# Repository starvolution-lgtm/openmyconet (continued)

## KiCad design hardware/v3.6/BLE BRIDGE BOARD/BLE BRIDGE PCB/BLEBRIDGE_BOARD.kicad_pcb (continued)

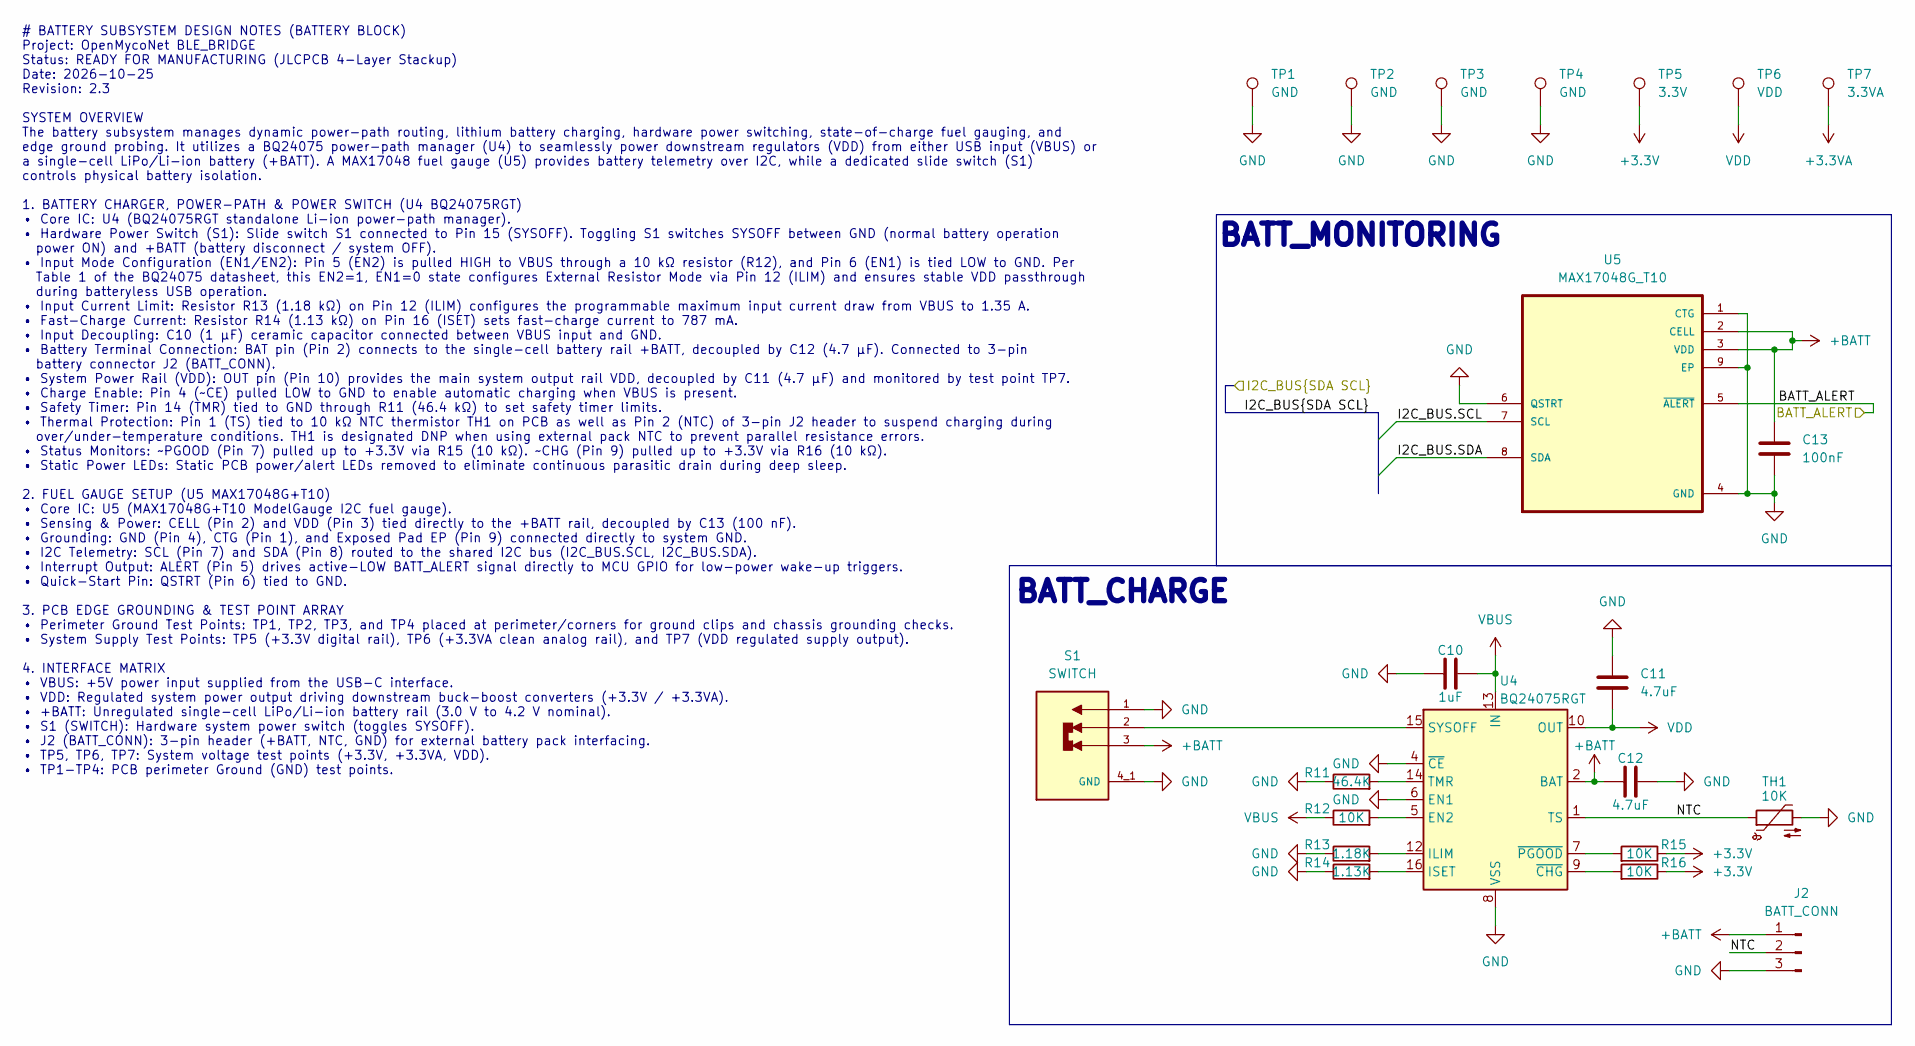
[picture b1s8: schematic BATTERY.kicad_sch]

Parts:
C10: 1uF; C_0805_2012Metric
C11, C12: 4.7uF; C_0805_2012Metric
C13: 100nF; C_0603_1608Metric
J2: BATT_CONN; JST_XH_B3B-XH-A_1x03_P2.50mm_Vertical
R11: 46.4K; R_0603_1608Metric
R12, R15, R16: 10K; R_0603_1608Metric
R13: 1.18K; R_0603_1608Metric
R14: 1.13K; R_0603_1608Metric
S1: SWITCH; SW_MSK12C02; PARTREV A/0
TH1: 10K; R_0805_2012Metric
TP1, TP2, TP3, TP4: GND; TestPoint_Plated_Hole_D2.0mm
TP5: 3.3V; TestPoint_Pad_1.0x1.0mm
TP6: VDD; TestPoint_Pad_1.0x1.0mm
TP7: 3.3VA; TestPoint_Pad_1.0x1.0mm
U4: BQ24075RGT; VQFN-16-1EP_3x3mm_P0.5mm_EP1.6x1.6mm
U5: MAX17048G_T10; SON50P200X200X80-9N

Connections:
+3.3V: R15.1, R16.1, TP5.1 (1_1); also elsewhere on the board
+3.3VA: TP7.1 (1_1); also elsewhere on the board
+BATT: C12.2, C13.1, J2.1, S1.3, U4.2 (BAT), U4.3 (BAT), U5.2 (CELL), U5.3 (VDD)
/BLOCK_DIAGRAM//BATT_ALERT: U5.5 (~ALERT); also elsewhere on the board
/BLOCK_DIAGRAM//I2C_BUS.SCL: U5.7 (SCL); also elsewhere on the board
/BLOCK_DIAGRAM//I2C_BUS.SDA: U5.8 (SDA); also elsewhere on the board
/BLOCK_DIAGRAM/BATTERY/NTC: J2.2, TH1.1, U4.1 (TS)
GND: C10.2, C11.1, C12.1, C13.2, J2.3, R11.1, R13.1, R14.1, S1.1, S1.4_1 (GND), S1.4_2 (GND), S1.4_3 (GND), S1.4_4 (GND), TH1.2, TP1.1 (1_1), TP2.1 (1_1), TP3.1 (1_1), TP4.1 (1_1), U4.4 (~CE), U4.6 (EN1), U4.8 (VSS), U4.17 (VSS), U5.1 (CTG), U5.4 (GND), U5.6 (QSTRT), U5.9 (EP); also elsewhere on the board
unnamed: R12.2, U4.5 (EN2)
unnamed: R13.2, U4.12 (ILIM)
unnamed: R14.2, U4.16 (ISET)
unnamed: S1.2, U4.15 (SYSOFF)
unnamed: R11.2, U4.14 (TMR)
unnamed: R16.2, U4.9 (~CHG)
unnamed: R15.2, U4.7 (~PGOOD)
VBUS: C10.1, R12.1, U4.13 (IN); also elsewhere on the board
VDD: C11.2, TP6.1 (1_1), U4.10 (OUT), U4.11 (OUT); also elsewhere on the board

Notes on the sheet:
BATT_CHARGE
# BATTERY SUBSYSTEM DESIGN NOTES (BATTERY BLOCK) Project: OpenMycoNet BLE_BRIDGE Status: READY FOR MANUFACTURING (JLCPCB 4-Layer Stackup) Date: 2026-10-25 Revision: 2.3 SYSTEM OVERVIEW The battery subsystem manages dynamic power-path routing, lithium battery charging, hardware power switching, stat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
BATT_MONITORING

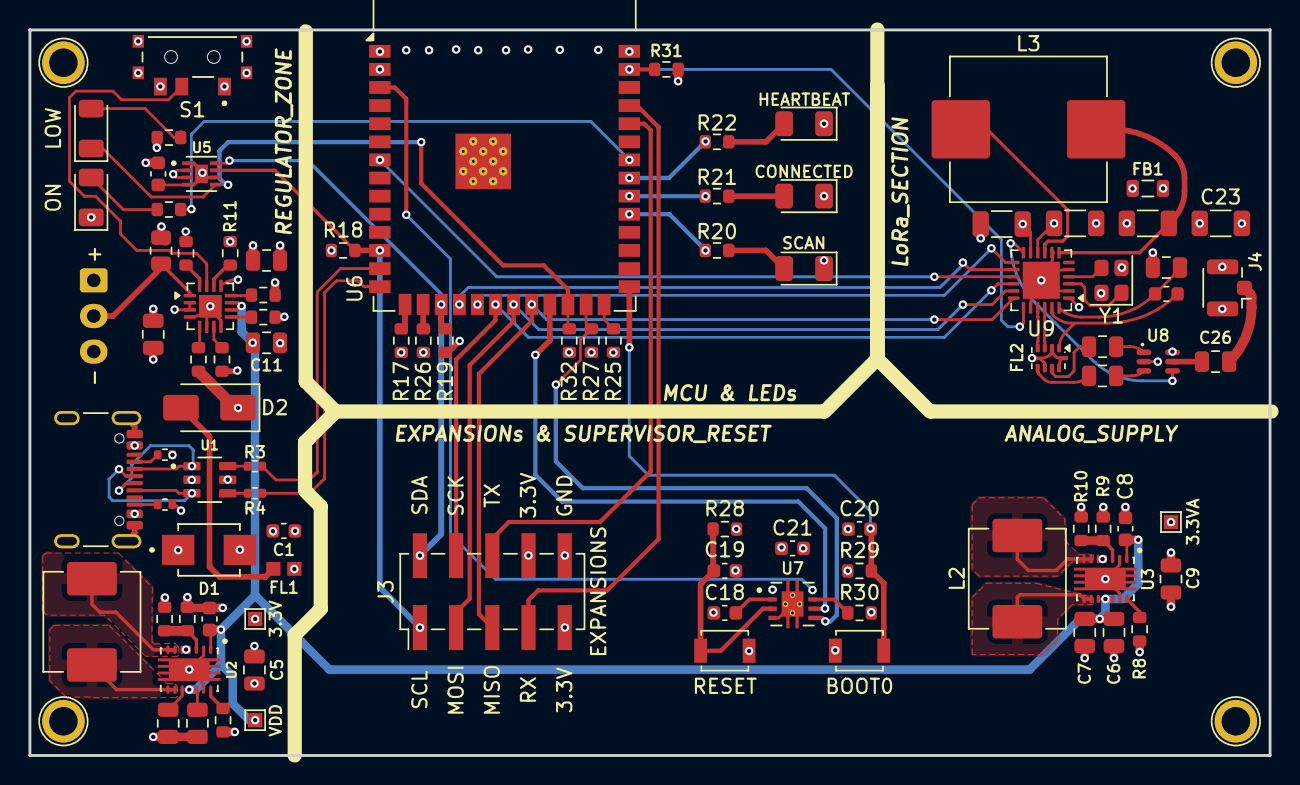
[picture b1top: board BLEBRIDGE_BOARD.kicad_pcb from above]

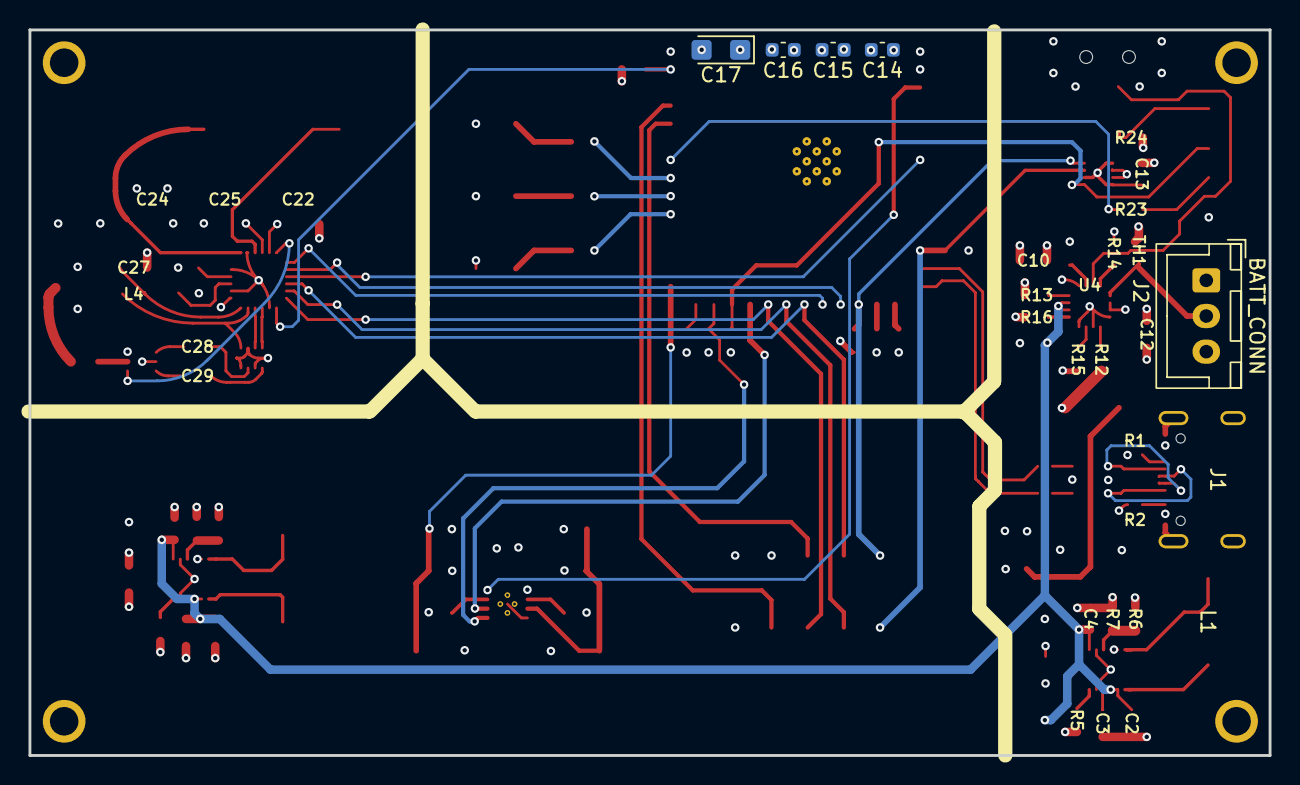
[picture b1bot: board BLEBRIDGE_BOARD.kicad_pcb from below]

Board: 4 copper layers, 87.0 x 50.9 mm, 100 parts (5 on the bottom side), 79 nets.

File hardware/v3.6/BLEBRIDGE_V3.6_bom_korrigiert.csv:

Designator,Footprint,Quantity,Value,LCSC Part #
"C1, C13, C14, C15, C16, C18, C19, C20, C21, C4, C8",603,11,100nF,
C10,805,1,1uF,
"C11, C12",805,2,4.7uF,
C17,CP_EIA-3216-18_Kemet-A,1,10uF,C7171
"C2, C3, C5, C6, C7, C9",805,6,10uF,
C22,1206,1,10uF,
C23,1206,1,100nF,
C24,1206,1,470nF,
C25,1206,1,47uF,
"C26, C28, C29",805,3,47pF,
C27,805,1,100nF,
D1,SMBJ5.0A,1,SMBJ5.0A,C83333
D2,D_SMA,1,SS34,C8678
D3,1206,1,LOW,C28310439
D4,1206,1,SCAN,C28310438
D5,1206,1,CONNECTED,C30584802
D6,1206,1,HEARTBEAT,C28310440
D7,1206,1,ON,C30584801
FB1,805,1,FerriteBead_Small,
FL1,BEADC1608X95N,1,BLM18PG121SN1D,C14709
FL2,Balun_Johanson_0900FM15K0039,1,0900FM15K0039,C7434807
J1,USB_C_Receptacle_GCT_USB4105-xx-A_16P_TopMnt_Horizontal,1,USB_C_Receptacle_USB2.0_16P,C2765186
J2,JST_XH_B3B-XH-A_1x03_P2.50mm_Vertical,1,BATT_CONN,C144394
J3,PinHeader_2x05_P2.54mm_Vertical_SMD,1,EXPANSIONS,C55213916
J4,U.FL_Hirose_U.FL-R-SMT-1_Vertical,1,Conn_Coaxial_Small,C88374
"L1, L2",L_APV_APH0630,2,1.5uH,C5349697
L3,L_APV_APH1040,1,15uH,C5349716
L4,603,1,27nH,C6807996
"R1, R2",402,2,5.1K,
"R10, R7",603,2,180K,
R11,603,1,46.4K,
"R12, R15, R16, R17, R25, R26, R28, R29, R31, R32",603,10,10K,
R13,603,1,1.18K,
R14,603,1,1.13K,
"R18, R19",603,2,4.7K,
"R20, R21, R22, R23, R24",603,5,1K,
"R27, R30, R5, R8",603,4,100K,
"R3, R4",402,2,27,
"R6, R9",603,2,1M,
S1,SW_MSK12C02,1,SWITCH,C431540
SW1,SW_SPST_B3U-1000P,1,RESET,C231329
SW2,SW_SPST_B3U-1000P,1,BOOT0,C231329
"TP1, TP2, TP3, TP4",TestPoint_Plated_Hole_D2.0mm,4,GND,
TP5,TestPoint_Pad_1.0x1.0mm,1,3.3V,
TP6,TestPoint_Pad_1.0x1.0mm,1,VDD,
TP7,TestPoint_Pad_1.0x1.0mm,1,3.3VA,
U1,USBLC6-2SC6,1,USBLC6-2SC6,C7519
"U2, U3",IC_TPS63020DSJT,2,TPS63020DSJR,C15483
U4,VQFN-16-1EP_3x3mm_P0.5mm_EP1.6x1.6mm,1,BQ24075RGT,C2865459
U5,SON50P200X200X80-9N,1,MAX17048G_T10,C2682616
U6,ESP32-S3-WROOM-1,1,ESP32-S3-WROOM-1-N16R8,C2913202
U7,IC_DRV8601DRBT,1,TPS3851H33EDRBR,C717624
U8,SOT65P215X110-6N,1,PE4259,C470892
U9,QFN-24-1EP_4x4mm_P0.5mm_EP2.6x2.6mm,1,SX1262IMLTRT,C191341
Y1,Crystal_SMD_2520-4Pin_2.5x2.0mm,1,32MHz,C2842280

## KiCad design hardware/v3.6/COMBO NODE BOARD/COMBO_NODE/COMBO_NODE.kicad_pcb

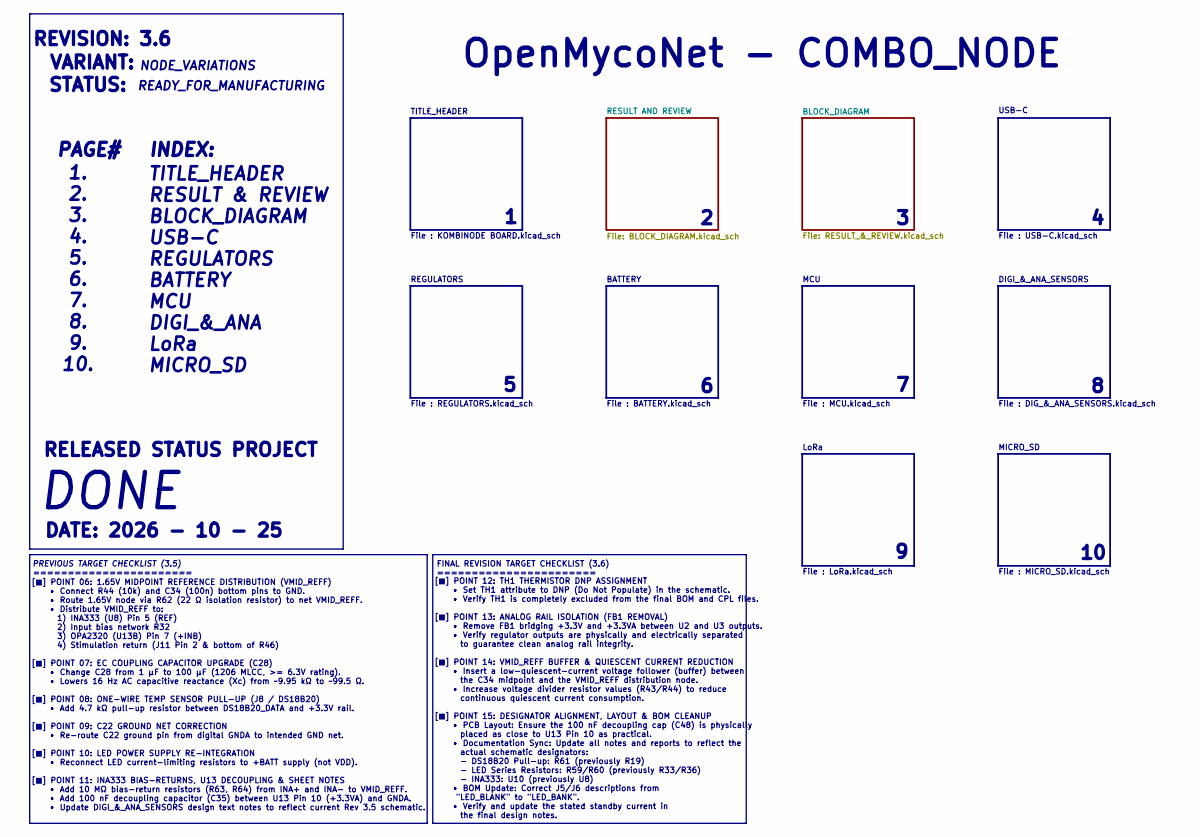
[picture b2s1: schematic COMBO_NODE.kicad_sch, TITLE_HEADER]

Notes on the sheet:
PAGE#
PREVIOUS TARGET CHECKLIST (3.5) =======================
File : LoRa.kicad_sch
MICRO_SD
USB-C
NODE_VARIATIONS
TITLE_HEADER
VARIANT:
File : MICRO_SD.kicad_sch
MCU
File : REGULATORS.kicad_sch
FINAL REVISION TARGET CHECKLIST (3.6) =======================
File : KOMBINODE BOARD.kicad_sch
INDEX:
REVISION: 3.6
BATTERY
STATUS:
DIGI_&_ANA_SENSORS
DONE
READY_FOR_MANUFACTURING
TITLE_HEADER RESULT & REVIEW BLOCK_DIAGRAM USB-C REGULATORS BATTERY MCU DIGI_&_ANA LoRa MICRO_SD
File : BATTERY.kicad_sch
[■] POINT 06: 1.65V MIDPOINT REFERENCE DISTRIBUTION (VMID_REFF) • Connect R44 (10k) and C34 (100n) bottom pins to GND. • Route 1.65V node via R62 (22 Ω isolation resistor) to net VMID_REFF. • Distribute VMID_REFF to: 1) INA333 (U8) Pin 5 (REF) 2) Input bias network R32 3) OPA2320 (U13B) Pin 7 (+INB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
File : MCU.kicad_sch
RELEASED STATUS PROJECT
DATE: 2026 - 10 - 25
LoRa
[■] POINT 12: TH1 THERMISTOR DNP ASSIGNMENT • Set TH1 attribute to DNP (Do Not Populate) in the schematic. • Verify TH1 is completely excluded from the final BOM and CPL files. [■] POINT 13: ANALOG RAIL ISOLATION (FB1 REMOVAL) • Remove FB1 bridging +3.3V and +3.3VA between U2 and U3 outputs. • Veri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
1. 2. 3. 4. 5. 6. 7. 8. 9. 10.
OpenMycoNet - COMBO_NODE
REGULATORS
File : USB-C.kicad_sch
File : DIG_&_ANA_SENSORS.kicad_sch

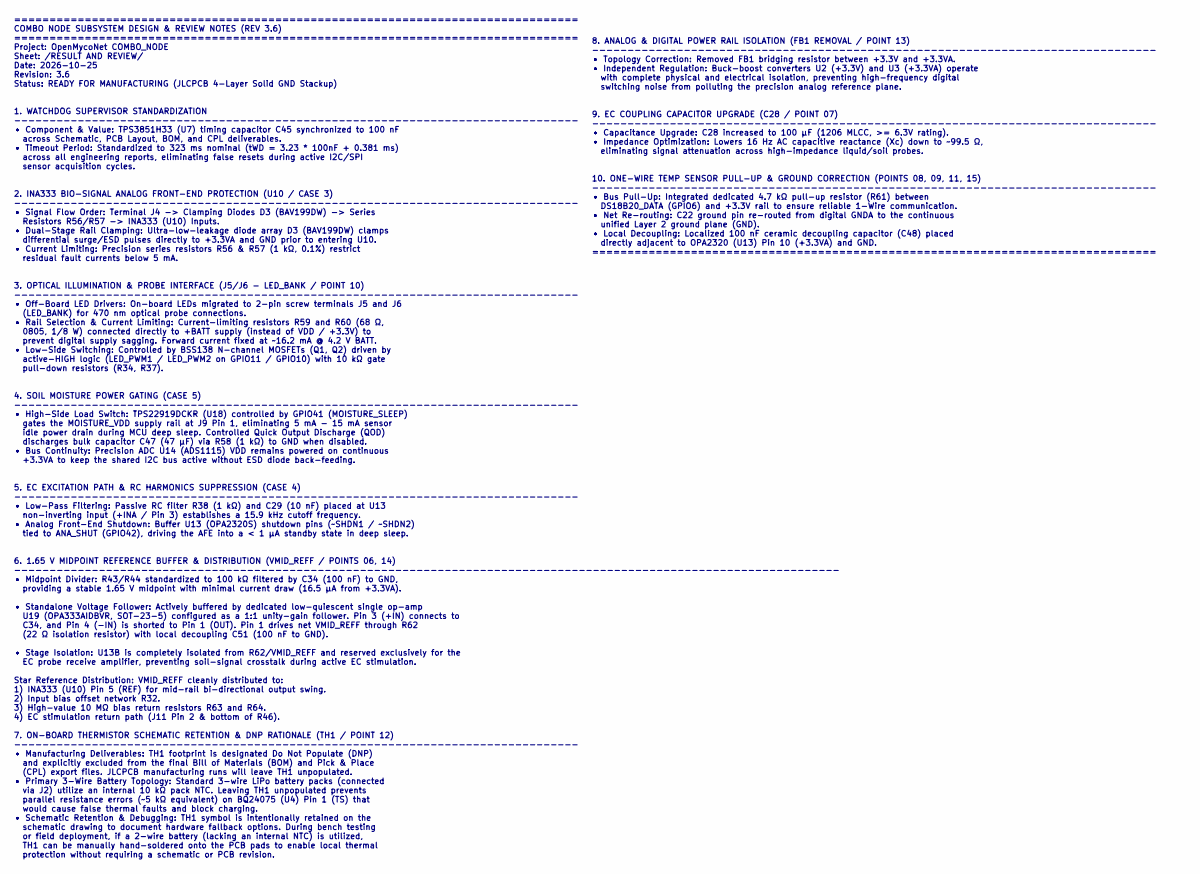
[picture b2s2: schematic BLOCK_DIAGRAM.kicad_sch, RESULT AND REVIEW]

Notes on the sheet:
8. ANALOG & DIGITAL POWER RAIL ISOLATION (FB1 REMOVAL / POINT 13) -------------------------------------------------------------------------------- • Topology Correction: Removed FB1 bridging resistor between +3.3V and +3.3VA. • Independent Regulation: Buck-boost converters U2 (+3.3V) and U3 (+3.3VA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
================================================================================ COMBO NODE SUBSYSTEM DESIGN & REVIEW NOTES (REV 3.6) ================================================================================ Project: OpenMycoNet COMBO_NODE Sheet: /RESULT AND REVIEW/ Date: 2026-10-25 Revision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

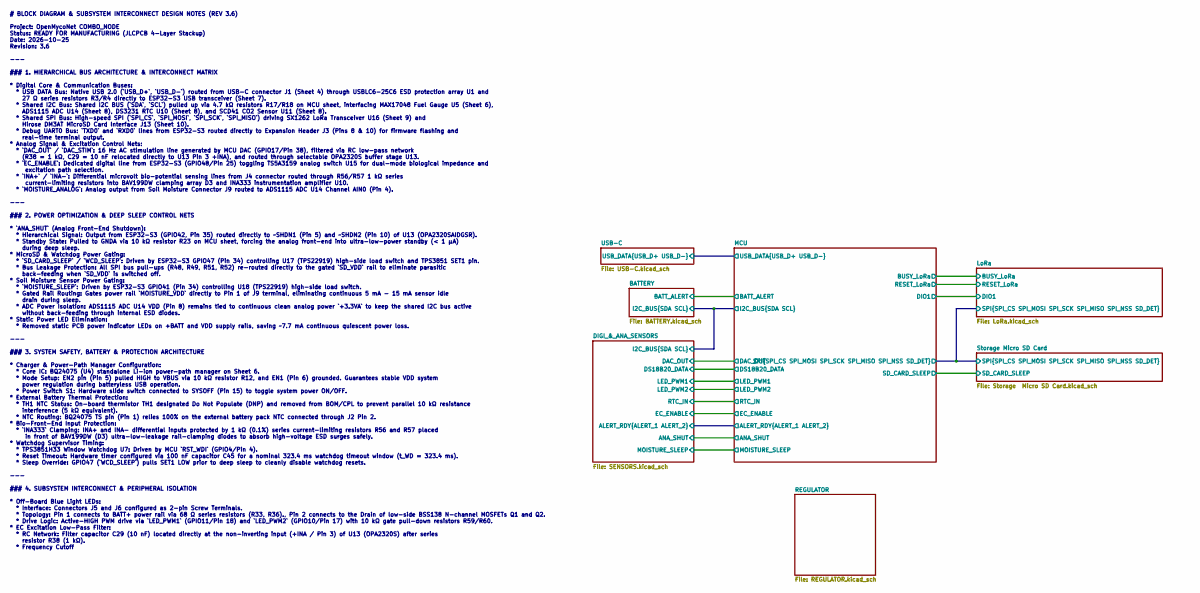
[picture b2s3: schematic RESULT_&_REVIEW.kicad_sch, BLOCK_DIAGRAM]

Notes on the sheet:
# BLOCK DIAGRAM & SUBSYSTEM INTERCONNECT DESIGN NOTES (REV 3.6) Project: OpenMycoNet COMBO_NODE Status: READY FOR MANUFACTURING (JLCPCB 4-Layer Stackup) Date: 2026-10-25 Revision: 3.6 --- ### 1. HIERARCHICAL BUS ARCHITECTURE & INTERCONNECT MATRIX * Digital Core & Communication Buses: * USB DATA Bus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

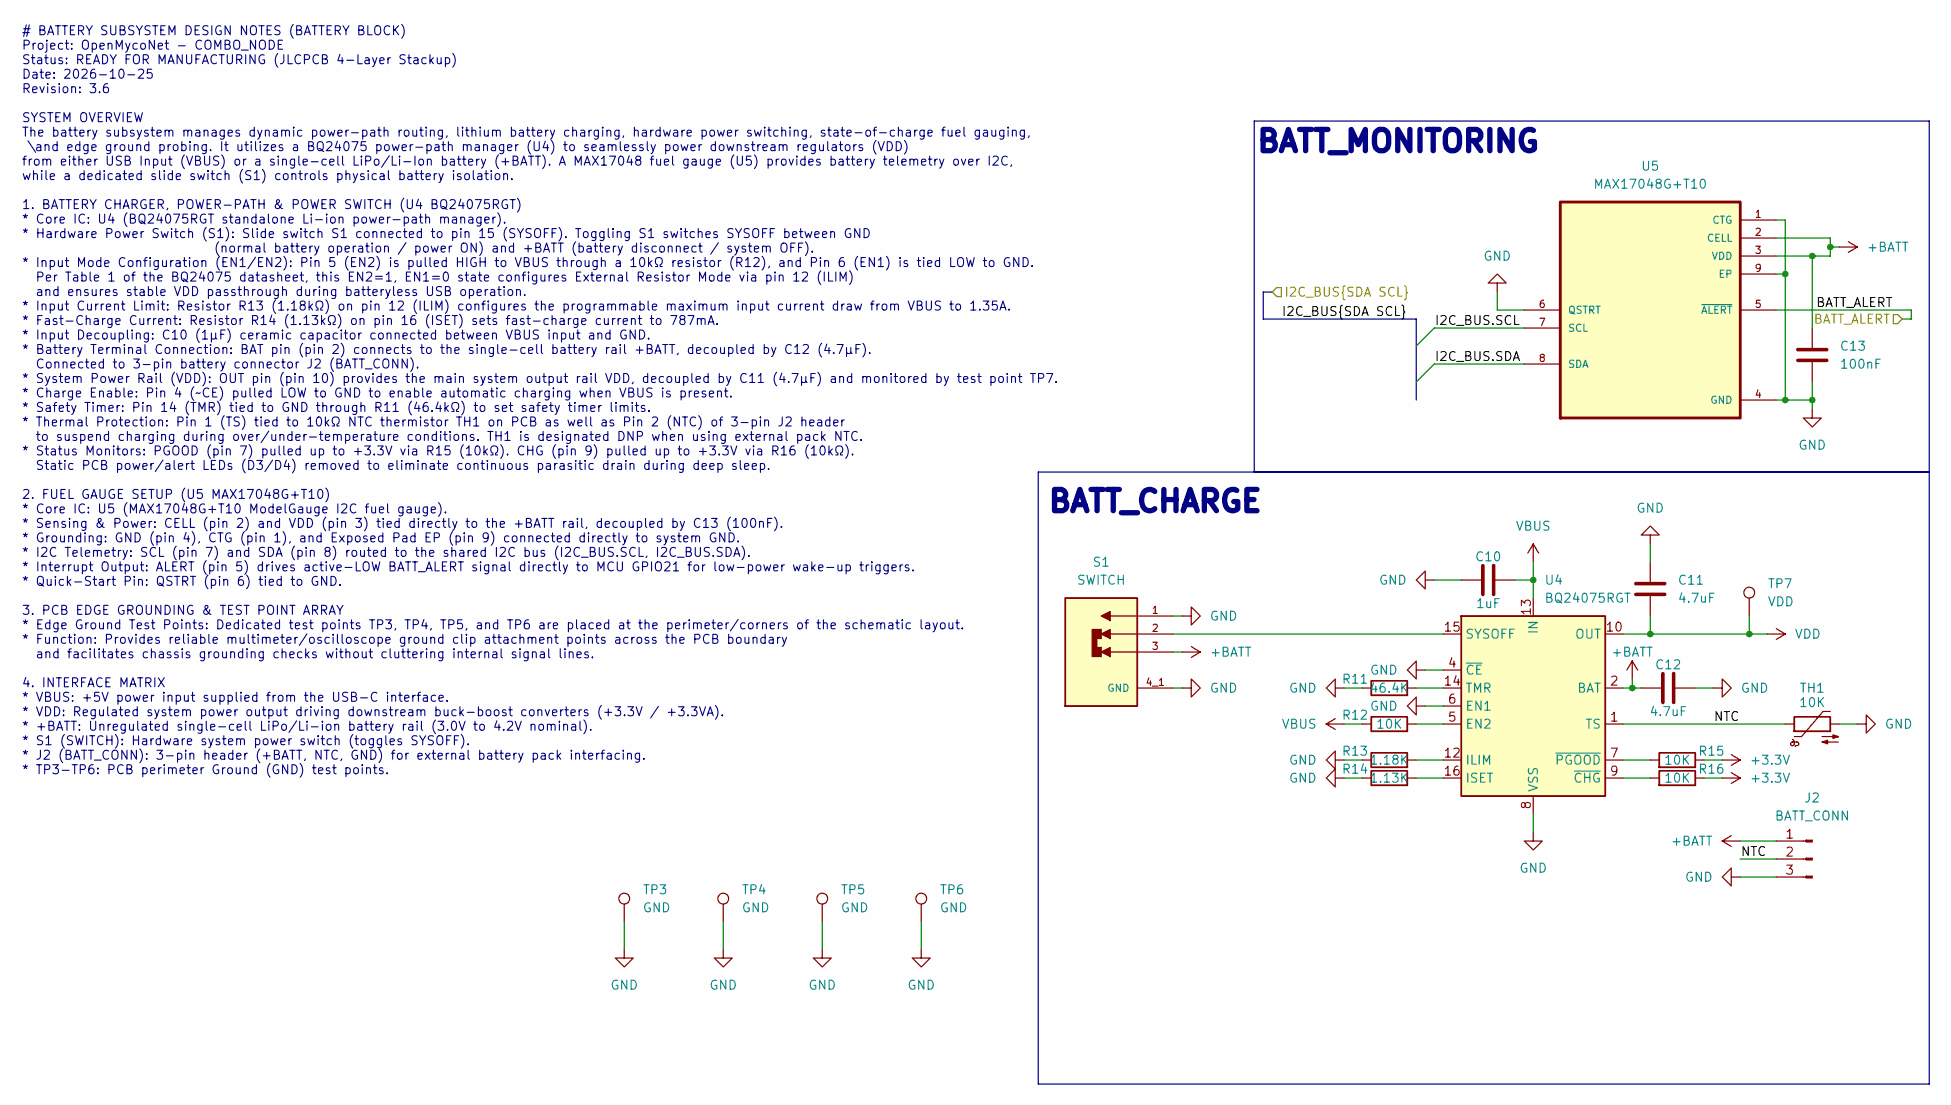
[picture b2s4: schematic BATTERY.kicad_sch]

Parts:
C10: 1uF; C_0805_2012Metric
C11, C12: 4.7uF; C_0805_2012Metric
C13: 100nF; C_0603_1608Metric
J2: BATT_CONN; JST_XH_B3B-XH-A_1x03_P2.50mm_Vertical
R11: 46.4K; R_0603_1608Metric
R12, R15, R16: 10K; R_0603_1608Metric
R13: 1.18K; R_0603_1608Metric
R14: 1.13K; R_0603_1608Metric
S1: SWITCH; SW_MSK12C02; PARTREV A/0
TH1: 10K; R_0805_2012Metric
TP3, TP4, TP5, TP6: GND; TestPoint_Plated_Hole_D2.0mm
TP7: VDD; TestPoint_Pad_1.0x1.0mm
U4: BQ24075RGT; VQFN-16-1EP_3x3mm_P0.5mm_EP1.6x1.6mm
U5: MAX17048G+T10; SON50P200X200X80-9N

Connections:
+3.3V: R15.1, R16.1; also elsewhere on the board
+BATT: C12.2, C13.1, J2.1, S1.3, U4.2 (BAT), U4.3 (BAT), U5.2 (CELL), U5.3 (VDD); also elsewhere on the board
/BLOCK_DIAGRAM/BATTERY/BATT_ALERT: U5.5 (~ALERT); also elsewhere on the board
/BLOCK_DIAGRAM/BATTERY/I2C_BUS.SCL: U5.7 (SCL); also elsewhere on the board
/BLOCK_DIAGRAM/BATTERY/I2C_BUS.SDA: U5.8 (SDA); also elsewhere on the board
/BLOCK_DIAGRAM/BATTERY/NTC: J2.2, TH1.1, U4.1 (TS)
GND: C10.2, C11.1, C12.1, C13.2, J2.3, R11.1, R13.1, R14.1, S1.1, S1.4_1 (GND), S1.4_2 (GND), S1.4_3 (GND), S1.4_4 (GND), TH1.2, TP3.1 (1_1), TP4.1 (1_1), TP5.1 (1_1), TP6.1 (1_1), U4.4 (~CE), U4.6 (EN1), U4.8 (VSS), U4.17 (VSS), U5.1 (CTG), U5.4 (GND), U5.6 (QSTRT), U5.9 (EP); also elsewhere on the board
unnamed: R12.2, U4.5 (EN2)
unnamed: R13.2, U4.12 (ILIM)
unnamed: R14.2, U4.16 (ISET)
unnamed: S1.2, U4.15 (SYSOFF)
unnamed: R11.2, U4.14 (TMR)
unnamed: R16.2, U4.9 (~CHG)
unnamed: R15.2, U4.7 (~PGOOD)
VBUS: C10.1, R12.1, U4.13 (IN); also elsewhere on the board
VDD: C11.2, TP7.1 (1_1), U4.10 (OUT), U4.11 (OUT); also elsewhere on the board

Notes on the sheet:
# BATTERY SUBSYSTEM DESIGN NOTES (BATTERY BLOCK) Project: OpenMycoNet - COMBO_NODE Status: READY FOR MANUFACTURING (JLCPCB 4-Layer Stackup) Date: 2026-10-25 Revision: 3.6 SYSTEM OVERVIEW The battery subsystem manages dynamic power-path routing, lithium battery charging, hardware power switching, st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
BATT_MONITORING
BATT_CHARGE

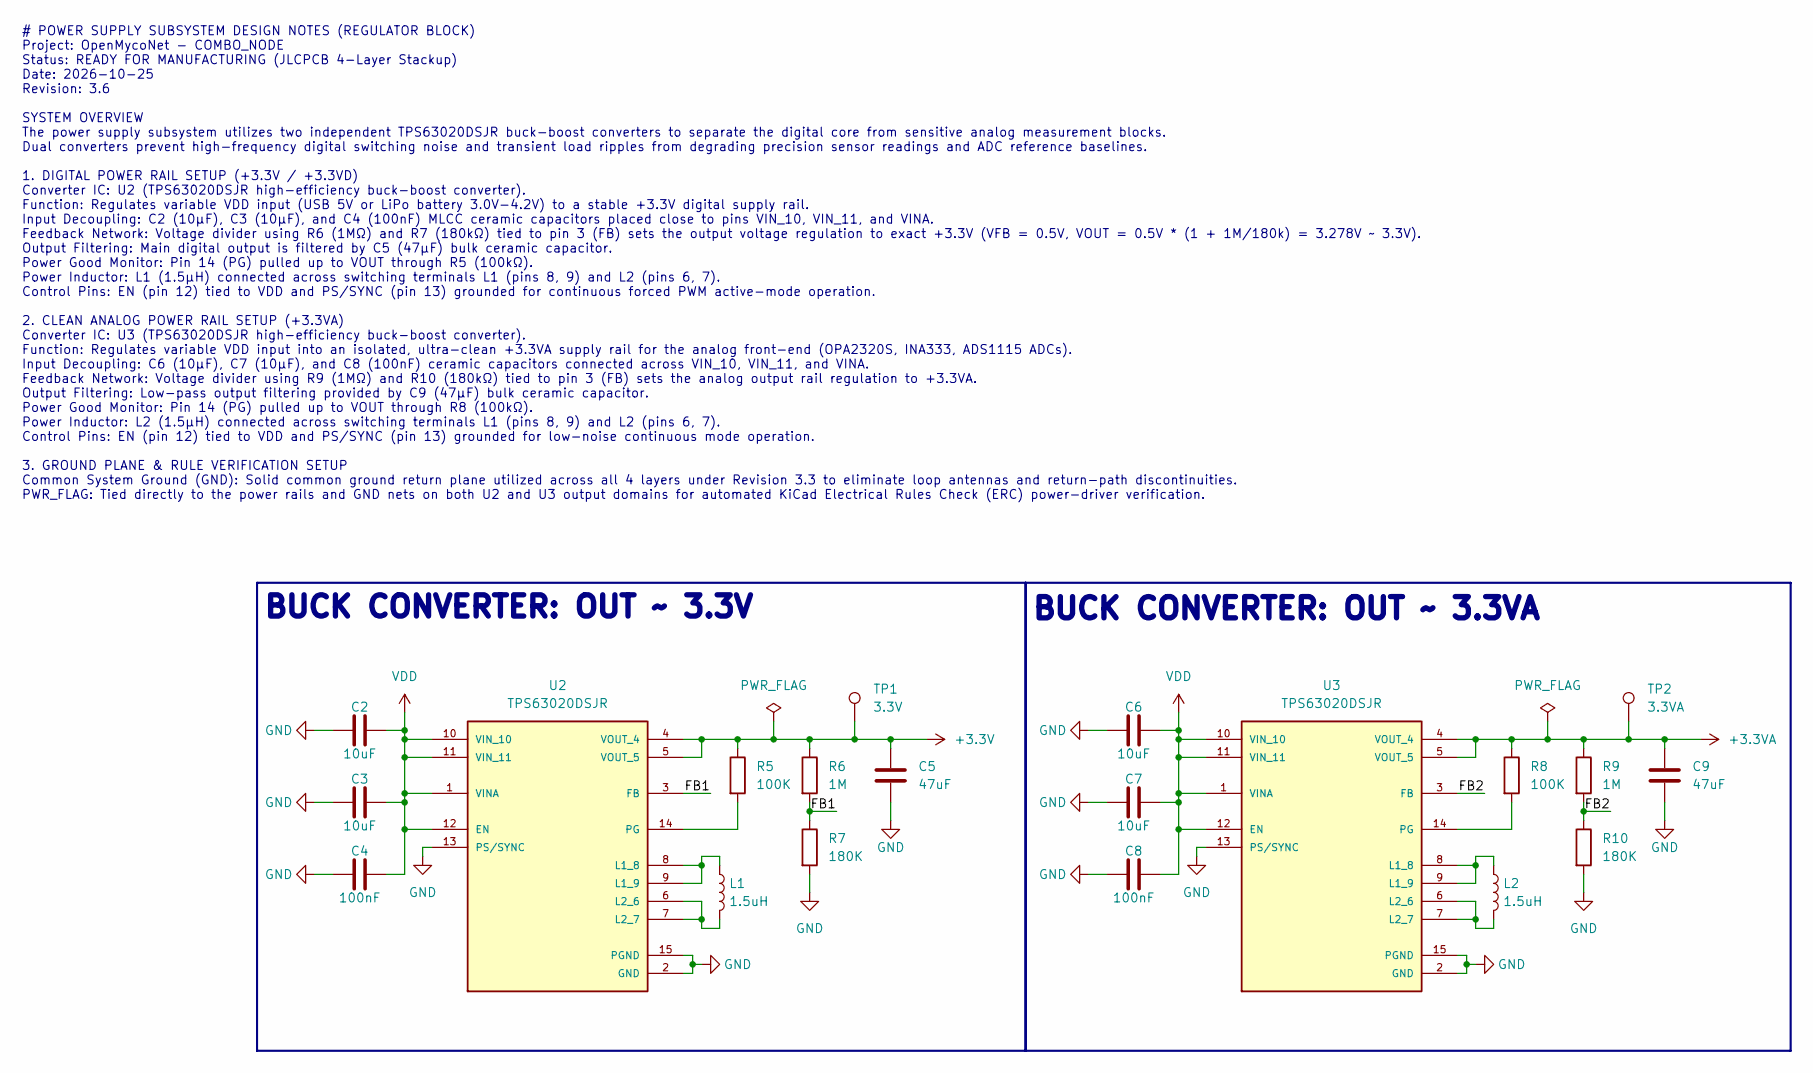
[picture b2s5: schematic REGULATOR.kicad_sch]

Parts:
C2, C3, C6, C7: 10uF; C_0805_2012Metric
C4, C8: 100nF; C_0603_1608Metric
C5, C9: 47uF; C_0805_2012Metric
L1, L2: 1.5uH; L_APV_APH0630
R5, R8: 100K; R_0603_1608Metric
R6, R9: 1M; R_0603_1608Metric
R7, R10: 180K; R_0603_1608Metric
TP1: 3.3V; TestPoint_Pad_1.0x1.0mm
TP2: 3.3VA; TestPoint_Pad_1.0x1.0mm
U2, U3: TPS63020DSJR; IC_TPS63020DSJT; PARTREV I

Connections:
+3.3V: C5.2, R5.1, R6.1, TP1.1 (1_1), U2.4 (VOUT_4), U2.5 (VOUT_5); also elsewhere on the board
+3.3VA: C9.2, R8.1, R9.1, TP2.1 (1_1), U3.4 (VOUT_4), U3.5 (VOUT_5); also elsewhere on the board
/BLOCK_DIAGRAM/REGULATOR/FB1: R6.2, R7.1, U2.3 (FB)
/BLOCK_DIAGRAM/REGULATOR/FB2: R9.2, R10.1, U3.3 (FB)
GND: C2.2, C3.2, C4.2, C5.1, C6.2, C7.2, C8.2, C9.1, R7.2, R10.2, U2.2 (GND), U2.13 (PS/SYNC), U2.15 (PGND), U3.2 (GND), U3.13 (PS/SYNC), U3.15 (PGND); also elsewhere on the board
unnamed: L1.1, U2.8 (L1_8), U2.9 (L1_9)
unnamed: L1.2, U2.6 (L2_6), U2.7 (L2_7)
unnamed: R5.2, U2.14 (PG)
unnamed: L2.1, U3.8 (L1_8), U3.9 (L1_9)
unnamed: L2.2, U3.6 (L2_6), U3.7 (L2_7)
unnamed: R8.2, U3.14 (PG)
VDD: C2.1, C3.1, C4.1, C6.1, C7.1, C8.1, U2.1 (VINA), U2.10 (VIN_10), U2.11 (VIN_11), U2.12 (EN), U3.1 (VINA), U3.10 (VIN_10), U3.11 (VIN_11), U3.12 (EN); also elsewhere on the board

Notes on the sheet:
# POWER SUPPLY SUBSYSTEM DESIGN NOTES (REGULATOR BLOCK) Project: OpenMycoNet - COMBO_NODE Status: READY FOR MANUFACTURING (JLCPCB 4-Layer Stackup) Date: 2026-10-25 Revision: 3.6 SYSTEM OVERVIEW The power supply subsystem utilizes two independent TPS63020DSJR buck-boost converters to separate the di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
BUCK CONVERTER: OUT ~ 3.3V
BUCK CONVERTER: OUT ~ 3.3VA
